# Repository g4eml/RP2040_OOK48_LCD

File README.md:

# RP2040 OOK48 LCD

## Description

This Project is an experimental test for a new Synchronous On Off Keying mode for use with weak signal microwave contacts.
The protocol is based on an idea from Andy G4JNT with input from several other UK Microwave Group Members. 
It is described in the document https://github.com/g4eml/RP2040_OOK48_LCD/blob/main/Documents/OOK48%20Protocol.pdf.

## Features

- Uses On/Off keying which is easier to implement than Frequency Shift keying on the higher microwave bands. 

- The data rate is similar to Morse code, so the module can be connected directly to the CW key input of any radio. 

- Real time visual confirmation of the message, character by character. No need to wait 30 seconds to see if the reception has succeeded.

- Uses the GPS 1 Pulse per second signal for accurate character synchronisation.  

- Optional 2 Seconds per character mode which increases the decode sensitiviy slightly. 

- Stand alone Device with LCD touch screen display. 

- No special programming hardware or software required. 

- Programming using the RP2040s built in standard boot loader. 

- 10 Preset Messages are saved to EEPROM for automatic load on power on. 

- Automatic calculation of QTH Lacator. Selectable for 6, 8 or 10 character accuracy. This locator can be inserted in any of the 10 Preset Messages. 

- Recording of messages to SD card for later viewing on a PC.

- USB Drive mode to allow downloading of SD card files to a PC.

- Also now includes encode/decode mode for Morse Code and decode only mode for JT4G and PI4 beacon signals.

## Operation Description

### Display
The display is split into 4 main areas. On the left are the Spectrum display and Waterfall. These are used to tune the reciever to the correct frequency. 

In OOK48 and Morse modes the Spectrum and Waterfall span from 500 Hz to 1100 Hz. Underneath the spectrum display there is an orange band which indicates the correct frequency range for decoding (centred on 800 Hz) . The receiver needs to be tuned such that the received tone falls withing this orange band. 

Received messages will appear at one character per second on the right hand side of the display. 

When Transmitting the Spectrum display is replaced with a RED box and the Text 'TX'. The transmitted message appears on the right hand side in red as it is sent.

In JT4G mode the spectrum and waterfall span 500Hz to 2 KHz. In PI4 mode the span is 500Hz to 1500 Hz.  There are 4 orange bands indicating the 4 data tone frequencies. The receiver needs to be tuned such that the received tones fall withing these orange bands.

### Controls

At the bottom of the screen there are 6 touch buttons.

Clear.   Clears the Message display.

Config. Displays a config page which allows settings to be changed.  

Record Button (Red Circle).  Displayed when a FAT formatted SD card is fitted. Click to start recording of text to the SD card. (GPS must be active). The filename will be based on the current date and time DDMMYY-HHMMSS.txt.

Stop Button (White Square). Displayed when recording is in progress. Click to stop recording. 

App Selecting this shows a new screen with three buttons which are used to select the required mode of operation. OOK48, JT4G Decoder or PI4 Decoder. When selected the system will reboot into the new mode. 

Set Tx.  This shows a menu of the 10 stored messages to be used for transmit. Selecting a messsage allows it to be edited on the next screen. Pressing the Enter Button saves the message.

Tx / Rx   Starts and stops the transmission of the currently selected Message. 

Touching the Waterfall display area of the screen will cycle through a selection of Tone detection ranges indicated by the width of the orange band. 
Available ranges are +-50 Hz, +_ 100Hz and the full width 500-1100 Hz.
Wider ranges require less accurate tuning but have a slightly higher chance of errors with weak signals. 

A 'Factory Reset' can be done by holding your finger on the display while powering on. This will clear the EEPROM to its default values and run the screen calibration routine. 

## USB Drive Mode. 

If an SD card is present there will be an additonal line visible on the Config Page. 'Activate USB Drive Mode" .  Clicking on this button will activate the USB Memory stick emulation mode. You can then connect the HMI module to a PC and the contents of its SD card will appear as a USB drive. This allows the download and deletion of the saved text files without removing the SD card. 

This mode can pnly be exited by powering off the module. 

## Config page settings

- Set Locator Length.  Allows selection of 6, 8 or 10 digit locators.

- Character Period. Selects the normal 1S per character or the optional 2 Seconds per character. Both ends of the link need to have the same settings. 

- GPS Baud Rate. Selects 9600 Baud for the older GPS modules or 38400 for more recent modules.

- GPS Test Mode. If selected the right hand side of the main scree will show the status of the GPS 1PPS signal and NMEA messages, these can be used to confirm the correct operation of the GPS module.
   
- Decode Mode. Selects Normal or Alternate mode. Normal mode is tolerant of frequency drift and chirping. Alternate mode needs a very stable drift free tone but is slightly more sensitive.

- Tx Timing Advance. Allows a fixed delay to be added to compensate for signal processing delays in the Tx chain. (such as DSP audio processing)

- Rx Timing Retard. Allows a fixed delay to be added to compensate for any signal processing delays in the Rx chain. (such as noise reduction)
 
- Default Morse WPM. This is the Morse code speed set at power on. This speed can be adjusted during Morse Reception using the two buttons on the Text Display. 

- Activate USB Drive Mode.  Allows the module to be connected to a PC where it will appear as a USB drive allowing the contents of the SD card to be read or deleted. The module must be powered off to exit this mode. 

- Exit. Return to the previous screen.

- Version Number. 

- Voltage Display. This shows the current battery voltage.  This reading may need calibrating for each module. Measure the true battery voltage with a multimeter. Touch the Displayed voltage and enter the measured value. Exit the calibration screen to save the new calibration value. 

## Hardware Requirements

This code was originally designed to work with the Elecrow CrowPanel Pico-3.5 inch 480x320 TFT LCD HMI Module. https://www.aliexpress.com/item/1005007250778536.html 

Note:- similar HMI Panels are available using the ESP32 processor chip. Make sure that you are purchasing the RP2040 version. 

However the correct module now appears to be difficult to obtain. A new interface board has been designed to allow a Raspberry Pi Pico to be fitted to a more easily available 3.5" TFT touch panel.

The LCD screen, controller chip and Touch Screen controller appear to be exactly the same as the original module.
 
If you are searching for these online the critical points are that it needs to be a 3.5" display  320 x 480 resolution with an ILI9488 controller and touch screen. 
There are lots of similar displays out there but the correct ones are usually Red and have 14 connections at one end of the board and 4 connections at the other. Be careful as these are also available without the touch screen. 
Full schematic and PCB designs are in the PCB V2 folder. 
Note that these alternative displays come in at least two different versions.The functionality is the same but the 3D printed enclosure has to be slightly different. The displays can be identified by the position of the flex cable to the touch screen. On the 'Type A' display the flex cable is nearest to the 14 pin connector. On the 'Type B' display the flex cable is nearest to the 4 pin connector. The picture above shows the 'Type A' display.

A GPS module is also essential and must have a 1 Pulse per second output. This pulse is used to synchronise the start of each character. 

## Connecting

### Elecrow module

The receiver is connected to the HMI module via a simple level shifting interface. Details are shown in this document [Connections](Documents/Schematic.pdf)

The  GPS module can be connected the Connector on the top of the module as per the schematic. Alternatively it can be connected to the UART1 connector on the lower edge of the MHI Module. However the 1PPS signal will still need to be connected to the top connector. 

The power is provided by the USB-C connector marked 'USB' on the end of the HMI module, or optionally by a 3.7V lithium cell connected to the BAT connector. 

### New PCB

All of the interfacing components are included on the new PCB. Connect the radio and GPS modules to the marked connectors. A Single Cell Lithium battery can be connected to the BAT connector and an ON/OFF switch to the SW connector. 

## Programming or updating the HMI Module (quick method) 

1. Locate the latest compiled firmware file 'RP2040_OOK48_LCD.uf2' which will be found here https://github.com/g4eml/RP2040_OOK48_LCD/releases and save it to your desktop. 

2. Connect the Module to your PC using the USB-C port. 

3. If using the Elecraft module hold down the BOOT button on the back of the HMI module and briefly press the Reset button. If using the New PCB remove the power and hold down the BOOT button on the Pico while re-applying the power. The RP2040 should appear as a USB disk drive on your PC.

3. Copy the .uf2 file onto the USB drive. The RP2040 will recognise the file and immediately update its firmware and reboot.

## Building your own version of the firmware (longer method and not normally required unless you need to make changes)

The RP2040 is programmed using the Arduino IDE with the Earl F. Philhower, III  RP2040 core. 

#### Installing the Arduino IDE

1. Download and Install the Arduino IDE 2.3.0 from here https://www.arduino.cc/en/software

2. Open the Arduino IDE and go to File/Preferences.

3. in the dialog enter the following URL in the 'Additional Boards Manager URLs' field: https://github.com/earlephilhower/arduino-pico/releases/download/global/package_rp2040_index.json

4. Hit OK to close the Dialog.

5. Go to Tools->Board->Board Manager in the IDE.

6. Type “RP2040” in the search box.

7. Locate the entry for 'Raspberry Pi Pico/RP2040 by Earle F. Philhower, III' and click 'Install'

### Installing the required libraries

1. From the Arduino IDE select (Tools > Manage Libraries)
2. Search for 'arduinoFFT' Scroll down to find the arduinoFFT library by Enrique Condes.
3. Click Install
4. Now search for 'TFT_eSPI' and find the TFT graphics library by Bodmer.
5. Click Install
6. Now search for 'SdFat - Adafruit Fork" and find the library by Bill Greiman.
7. Click Install

#### Downloading the Software.

1. Download the latest released source code .zip file from https://github.com/g4eml/RP2040_OOK48_LCD/releases

2. Save it to a convenient location and then unzip it. 

The TFT_eSPI Library is unusual in that it needs to be configured to the TFT display in use by modifying library files. 
The required modified versions of the files are located in the 'LCD-eSPI Settings' folder of this repository. 
Copy the files 'Setup_Elecraft_HMI.h' and 'User_Setup_Select.h' from  the downloaded 'LCD-eSPI Settings' folder to your Arduino libraries directory.
This will normaly be found at 'Documents/Arduino/libraries/TFT_eSPI'

#### Programming the RP2040

1. Open the Arduino IDE and click File/Open

2. Navigate to the File RP2404Synth/RP2040_OOK48_LCD.ino (downloaded in the previous step) and click Open.

3. Select Tools and make the following settings.

   Board: "Raspberry Pi Pico"

   Port: "UF2 Board"
   
   Debug Level: "None"

   Debug Port: "Disabled"

   C++ Exceptions: "Disabled"

   Flash Size: "2Mb (no FS)"

   CPU Speed: "200MHz"

   IP/Bluetooth Stack: "IPV4 Only"

   Optimise: "Small (-Os)(standard)"

   RTTI: "Disabled"

   Stack Protection: "Disabled"

   Upload Method: "Default (UF2)"

   USB Stack: "Adafruit TinyUSB"  

5. Connect the Module to the USB port, hold down the BOOT button while powering on. 

6. Click Sketch/Upload.

The Sketch should compile and upload automatically to the Pico. If the upload fails you may need to disconnect the module and then hold down the BOOT button while reconnecting. 

## Connections

The receiver audio is connected using a simple CR network to GPIO Pins GND, 3V3 and 28 on the top edge of the HMI Module. 
Details of this interface are in this file.  

IO Pin 6 is connected to to gate of an N channel Mosfet. The drain of this Mosfet is connected to the PTT input of the radio.
IO Pin 7 is connected to to gate of an N channel Mosfet. The drain of this Mosfet is connected to the Key input of the radio.   

The firmware requires the connection of a GPS module. This is used to accurately set the time and to generate the 1 Pulse per second signal used to synchromise the satrt of each character. Any GPS module with a 3V3 output and a 1PPS output can be used. It needs to output NMEA data at 9600 Baud or 38400 Baud. One of the G10A-F30 modules was used for development.
GPS data to the HMI module is connected to IO pin 5.
GPS data from the HMI module is connected to IO pin 4.
1 PPS pulse from the GPS module is conneced to IO pin 3.

## 3D Printed Enclosure

Files for 3D printable enclosures for the each of the display variants are included in the Enclosure directory. 

Additional parts required.
- 3 Phono Sockets for Audio Input, Key Output and PTT Output
- PAM8403 amplifier module with volume control. Wired in parallel with input audio to allow monitoring of the signal 
- 28mm Speaker 
- 18650 Lithium Cell. (can be switched with the audio amp voulme control on/off switch)

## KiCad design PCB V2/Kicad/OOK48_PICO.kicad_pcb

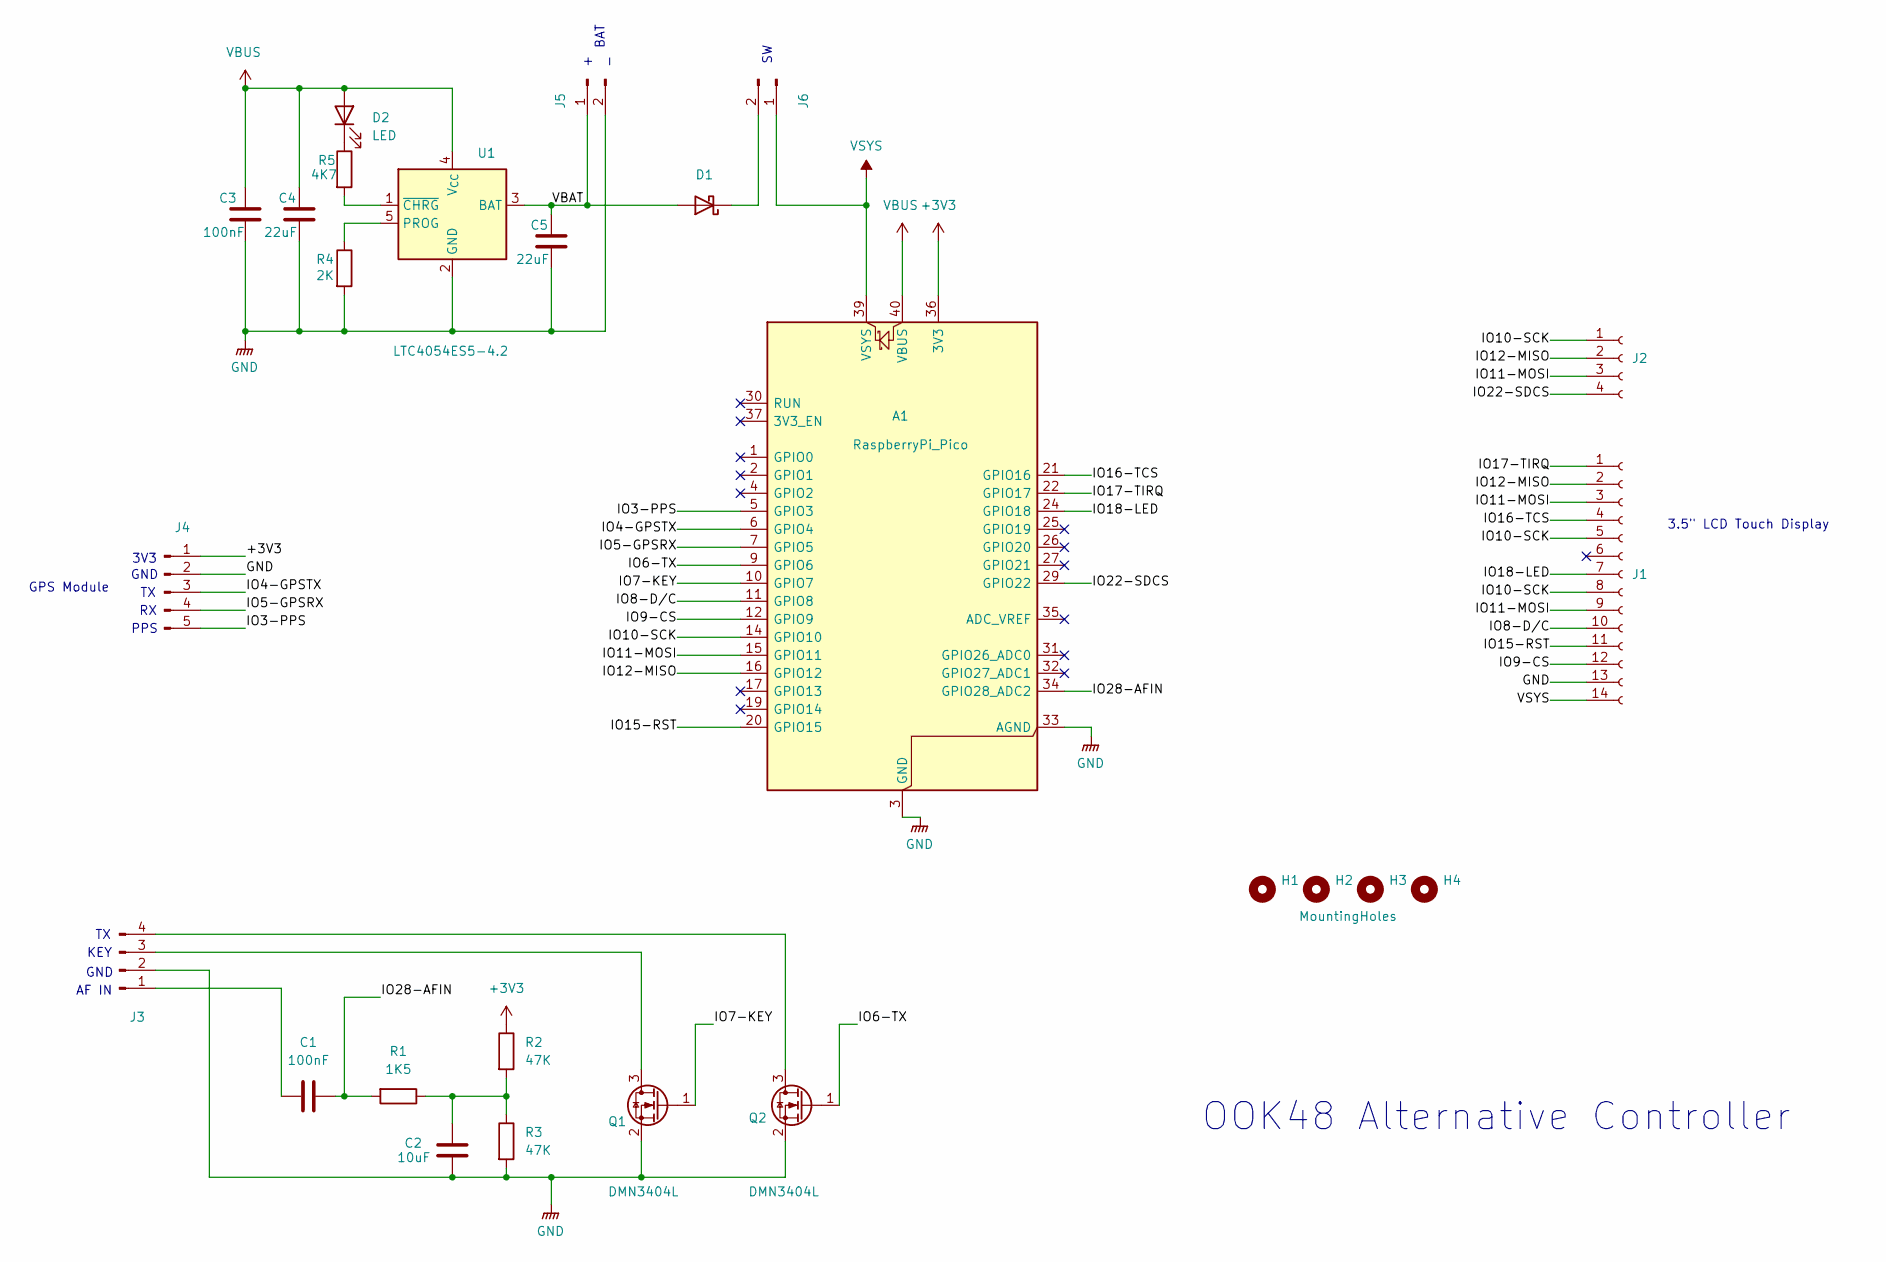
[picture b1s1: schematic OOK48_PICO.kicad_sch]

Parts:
A1: RaspberryPi_Pico; RaspberryPi_Pico_Common_THT
C1, C3: 100nF; C_0805_2012Metric_Pad1.18x1.45mm_HandSolder
C2: 10uF; C_0805_2012Metric_Pad1.18x1.45mm_HandSolder
C4, C5: 22uF; C_0805_2012Metric_Pad1.18x1.45mm_HandSolder
D1: D_Schottky; D_SOD-123F
D2: LED; LED_0805_2012Metric_Pad1.15x1.40mm_HandSolder
H1, H2, H3: MountingHole; MountingHole_3.2mm_M3_ISO14580_Pad
H4: MountingHoles; MountingHole_3.2mm_M3_ISO14580_Pad
J1: Conn_01x14_Socket; PinSocket_1x14_P2.54mm_Vertical
J2: Conn_01x04_Socket; PinSocket_1x04_P2.54mm_Vertical
J3: Conn_01x04_Pin; JST_XH_B4B-XH-A_1x04_P2.50mm_Vertical
J4: Conn_01x05_Pin; JST_XH_B5B-XH-A_1x05_P2.50mm_Vertical
J5, J6: Conn_01x02_Pin; JST_XH_B2B-XH-A_1x02_P2.50mm_Vertical
Q1, Q2: DMN3404L; SOT-23
R1: 1K5; C_0805_2012Metric_Pad1.18x1.45mm_HandSolder
R2, R3: 47K; C_0805_2012Metric_Pad1.18x1.45mm_HandSolder
R4: 2K; C_0805_2012Metric_Pad1.18x1.45mm_HandSolder
R5: 4K7; C_0805_2012Metric_Pad1.18x1.45mm_HandSolder
U1: LTC4054ES5-4.2; TSOT-23-5

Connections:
+3V3: A1.36 (3V3), J4.1, R2.1
/IO3-PPS: A1.5 (GPIO3), J4.5
/IO4-GPSTX: A1.6 (GPIO4), J4.3
/IO5-GPSRX: A1.7 (GPIO5), J4.4
/IO6-TX: A1.9 (GPIO6), Q2.1 (G)
/IO7-KEY: A1.10 (GPIO7), Q1.1 (G)
/IO8-D/C: A1.11 (GPIO8), J1.10
/IO9-CS: A1.12 (GPIO9), J1.12
/IO10-SCK: A1.14 (GPIO10), J1.5, J1.8, J2.1
/IO11-MOSI: A1.15 (GPIO11), J1.3, J1.9, J2.3
/IO12-MISO: A1.16 (GPIO12), J1.2, J2.2
/IO15-RST: A1.20 (GPIO15), J1.11
/IO16-TCS: A1.21 (GPIO16), J1.4
/IO17-TIRQ: A1.22 (GPIO17), J1.1
/IO18-LED: A1.24 (GPIO18), J1.7
/IO22-SDCS: A1.29 (GPIO22), J2.4
/IO28-AFIN: A1.34 (GPIO28_ADC2), C1.2, R1.2
/VBAT: C5.2, D1.2 (A), J5.1, U1.3 (BAT)
GND: A1.3 (GND), A1.8 (GND), A1.13 (GND), A1.18 (GND), A1.23 (GND), A1.28 (GND), A1.33 (AGND), A1.38 (GND), C2.1, C3.1, C4.1, C5.1, J1.13, J3.2, J4.2, J5.2, Q1.2 (S), Q2.2 (S), R3.2, R4.2, U1.2 (GND)
unnamed: C2.2, R1.1, R2.2, R3.1
unnamed: D1.1 (K), J6.2
unnamed: D2.1 (K), R5.1
unnamed: C1.1, J3.1
unnamed: J3.3, Q1.3 (D)
unnamed: J3.4, Q2.3 (D)
unnamed: R4.1, U1.5 (PROG)
unnamed: R5.2, U1.1 (~CHRG)
VBUS: A1.40 (VBUS), C3.2, C4.2, D2.2 (A), U1.4 (V_{CC})
VSYS: A1.39 (VSYS), J1.14, J6.1

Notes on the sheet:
KEY
GND
OOK48 Alternative Controller
GPS Module
BAT
PPS
3V3
3.5" LCD Touch Display
AF IN

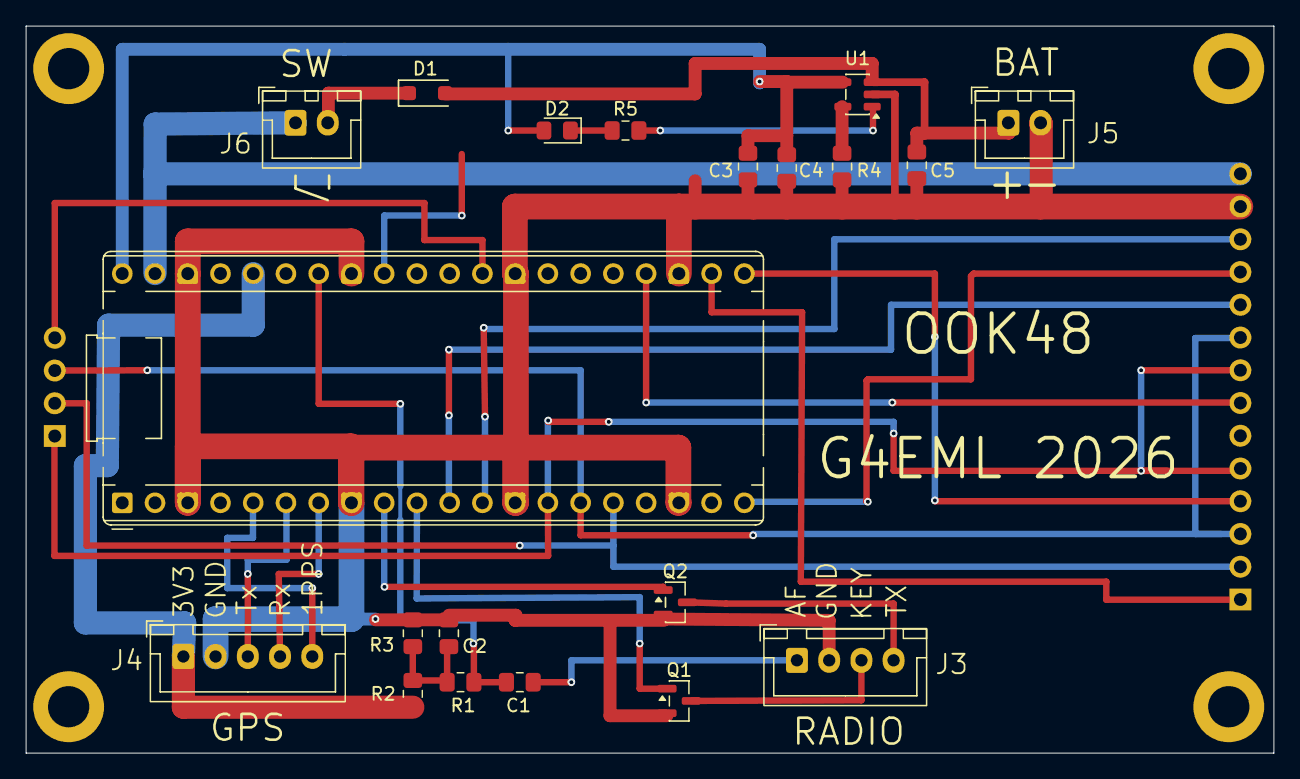
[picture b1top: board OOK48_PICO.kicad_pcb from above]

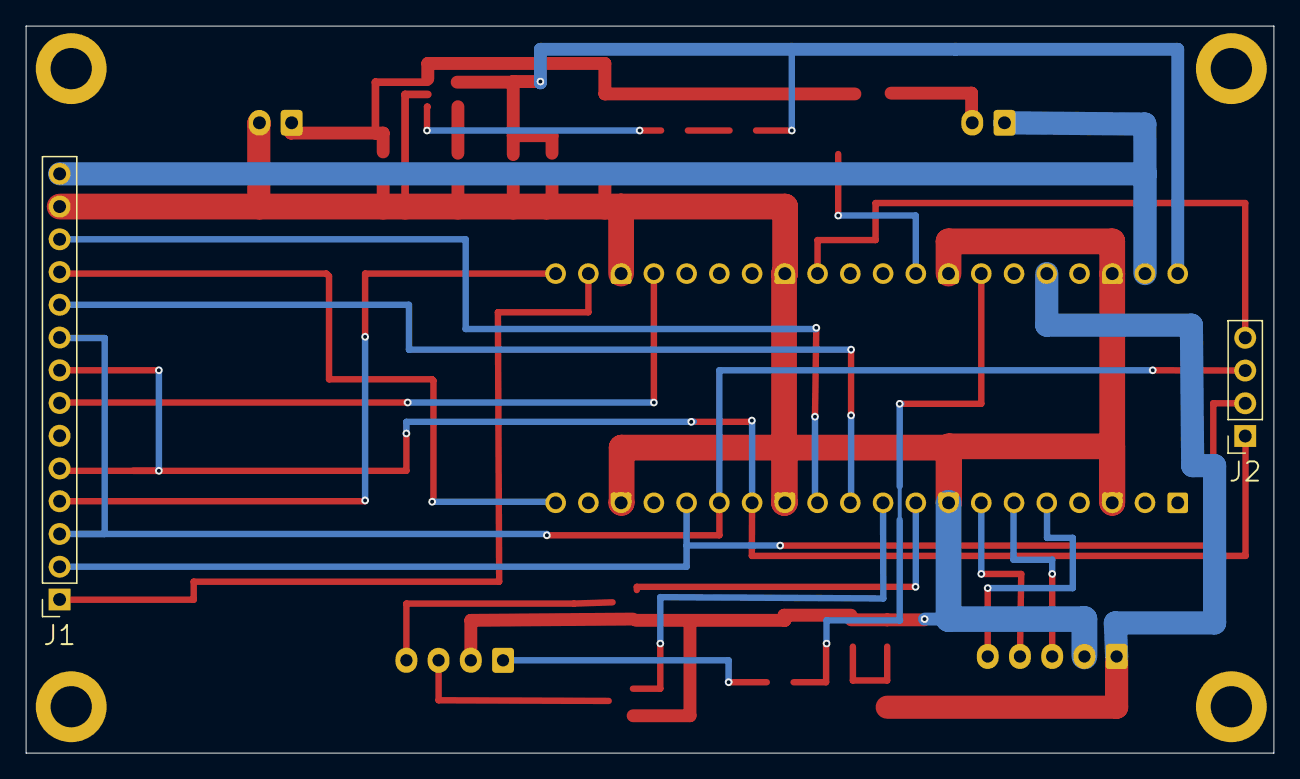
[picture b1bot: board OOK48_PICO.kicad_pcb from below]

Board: 2 copper layers, 96.8 x 56.4 mm, 26 parts (2 on the bottom side), 29 nets.

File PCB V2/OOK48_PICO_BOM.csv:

Reference,Qty,Value
A1,1,RaspberryPi_Pico
"C1,C3",2,100nF
C2,1,10uF
"C4,C5",2,22uF
D1,1,BAT42W
D2,1,0805 LED RED
J1,1,Conn_01x14_SIL  Socket
J2,1,Conn_01x04_SIL Socket
J3,1,JST_XH_B4B-XH-A
J4,1,JST_XH_B5B-XH-A
"J5,J6",2,:JST_XH_B2B-XH-A
"Q1,Q2",2,DMN3404L
R1,1,10K
"R2,R3",2,47K
R4,1,2K
R5,1,4K7
U1,1,LTC4054ES5-4.2

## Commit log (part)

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2025-06-09 Fix potential problem with 2 second mode.
2025-06-12 Use TFT_ESPi Buttons on main page
2025-06-19 Improve EEPROM Handling
2025-06-20 Add Locator Support
2025-06-21 Add Config Page
2025-06-21 fix compiler warning
2025-06-21 Fix Factory Reset
2025-07-05 Add Alternat Decoding Mode for less stable signals
2025-07-05 Add advance and retard to config items.
2025-07-05 add tx and rx delay
2025-07-05 Add CR at the start of each transmission
2025-07-08 tidy code
    Remove redundant threshold detection.
    Always use highest 4 of 8 for decoding.
    remove green flashing segment.
2025-07-08 tidy code
2025-07-09 add Version Number to config page
2025-07-09 Update Documents
2025-07-11 Add sample audio file
2025-07-21 Allow Message Change during Transmission.
2025-07-21 Change Default Decoding Mode
2025-07-22 Add SD card recording
2025-07-25 Add USB Drive Mode
2025-08-02 Use Goertzel instead of FFT
2025-08-03 use Goertzel
2025-08-07 Add 3D Enclosure files
2025-08-09 add 3d files
2025-08-09 Switch back to FFT
2025-08-10 Fix Half Rate
2025-08-10 Add battery voltage
2025-08-11 fix font glitch
2025-08-11 Add Battery Voltage calibration
2025-08-11 Remove Redundant Code
2025-08-12 Add Date to filenames + attributes
2025-09-07 Update Enclosure
2025-09-17 Update LCD setups
2026-03-01 Add NNew PCB Design
2026-03-01 Revise README for hardware and enclosure information
    Updated hardware requirements and enclosure details for clarity.
2026-03-02 Update GUI for Morse
2026-03-05 Initial commit of Morse
    Update GUI for Morse
2026-03-05 Add Morse Tx
2026-03-05 Loop Tx Messages
2026-03-06 add morse display during Tx
2026-03-06 Morse
2026-03-09 Discussion with Claude.ai to improve Lock times.
2026-03-09 More Claude AI improvements.
2026-03-10 Revert "Morse"
    This reverts commit 86adffc41fab511197d9ef20eb1cfb0b509a1558.
2026-03-10 Improve Legend display
2026-03-10 Remove Rainscatter Mode
    Remove Rainscatter Mode and Centroid tracking. Neither worked well.
2026-03-10 search range
2026-03-10 Another Claude AI assisted Update.
    Now responds better to speed changes and noisy signals. Getting better!.
2026-03-12 Add WPM Display and buttons
2026-03-13 Change to fixed speed Morse decoding
2026-03-13 add dot/dash ratio check
2026-03-13 Tidy
2026-03-13 Tidy Up
2026-03-15 Fix bugs before release
2026-03-15 Enhance README with Morse mode details
    Updated README to reflect new features in Morse mode and clarify functionality.
2026-03-16 Update 3D Enclosures
2026-03-17 Update new Box
2026-03-17 Improve Startup logic
2026-03-25 Reduce Touch pressure
    Some displays can't exceed 600 for Z pressure and so touches are not registered. Reduce this threshold to 300.
2026-03-26 Add Enclosure for typ B display
2026-03-26 Clarify 3D printed enclosure and display variants
    Updated README to clarify 3D printed enclosure details and display variants.
2026-03-26 Clarify Type A display identification in README
    Added a description of the 'Type A' display in the README.
2026-03-27 Add 500ms delay between tx and key down.
2026-03-29 Update PCB
2026-04-29 Fix LOC keyboard entry and add GPS Debug MEssages
2026-05-11 full settings clear on reset
2026-05-11 Include LOC in morse Tx
2026-05-14 corrrect error with morse '/'
